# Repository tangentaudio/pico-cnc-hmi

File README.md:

# pico-cnc-hmi
Open source and open hardware HMI for LinuxCNC using USB Raw HID on a Raspberry Pi Pico 2.

# News

- rev0 PCB sent to fabrication on 2025-MAR-10.

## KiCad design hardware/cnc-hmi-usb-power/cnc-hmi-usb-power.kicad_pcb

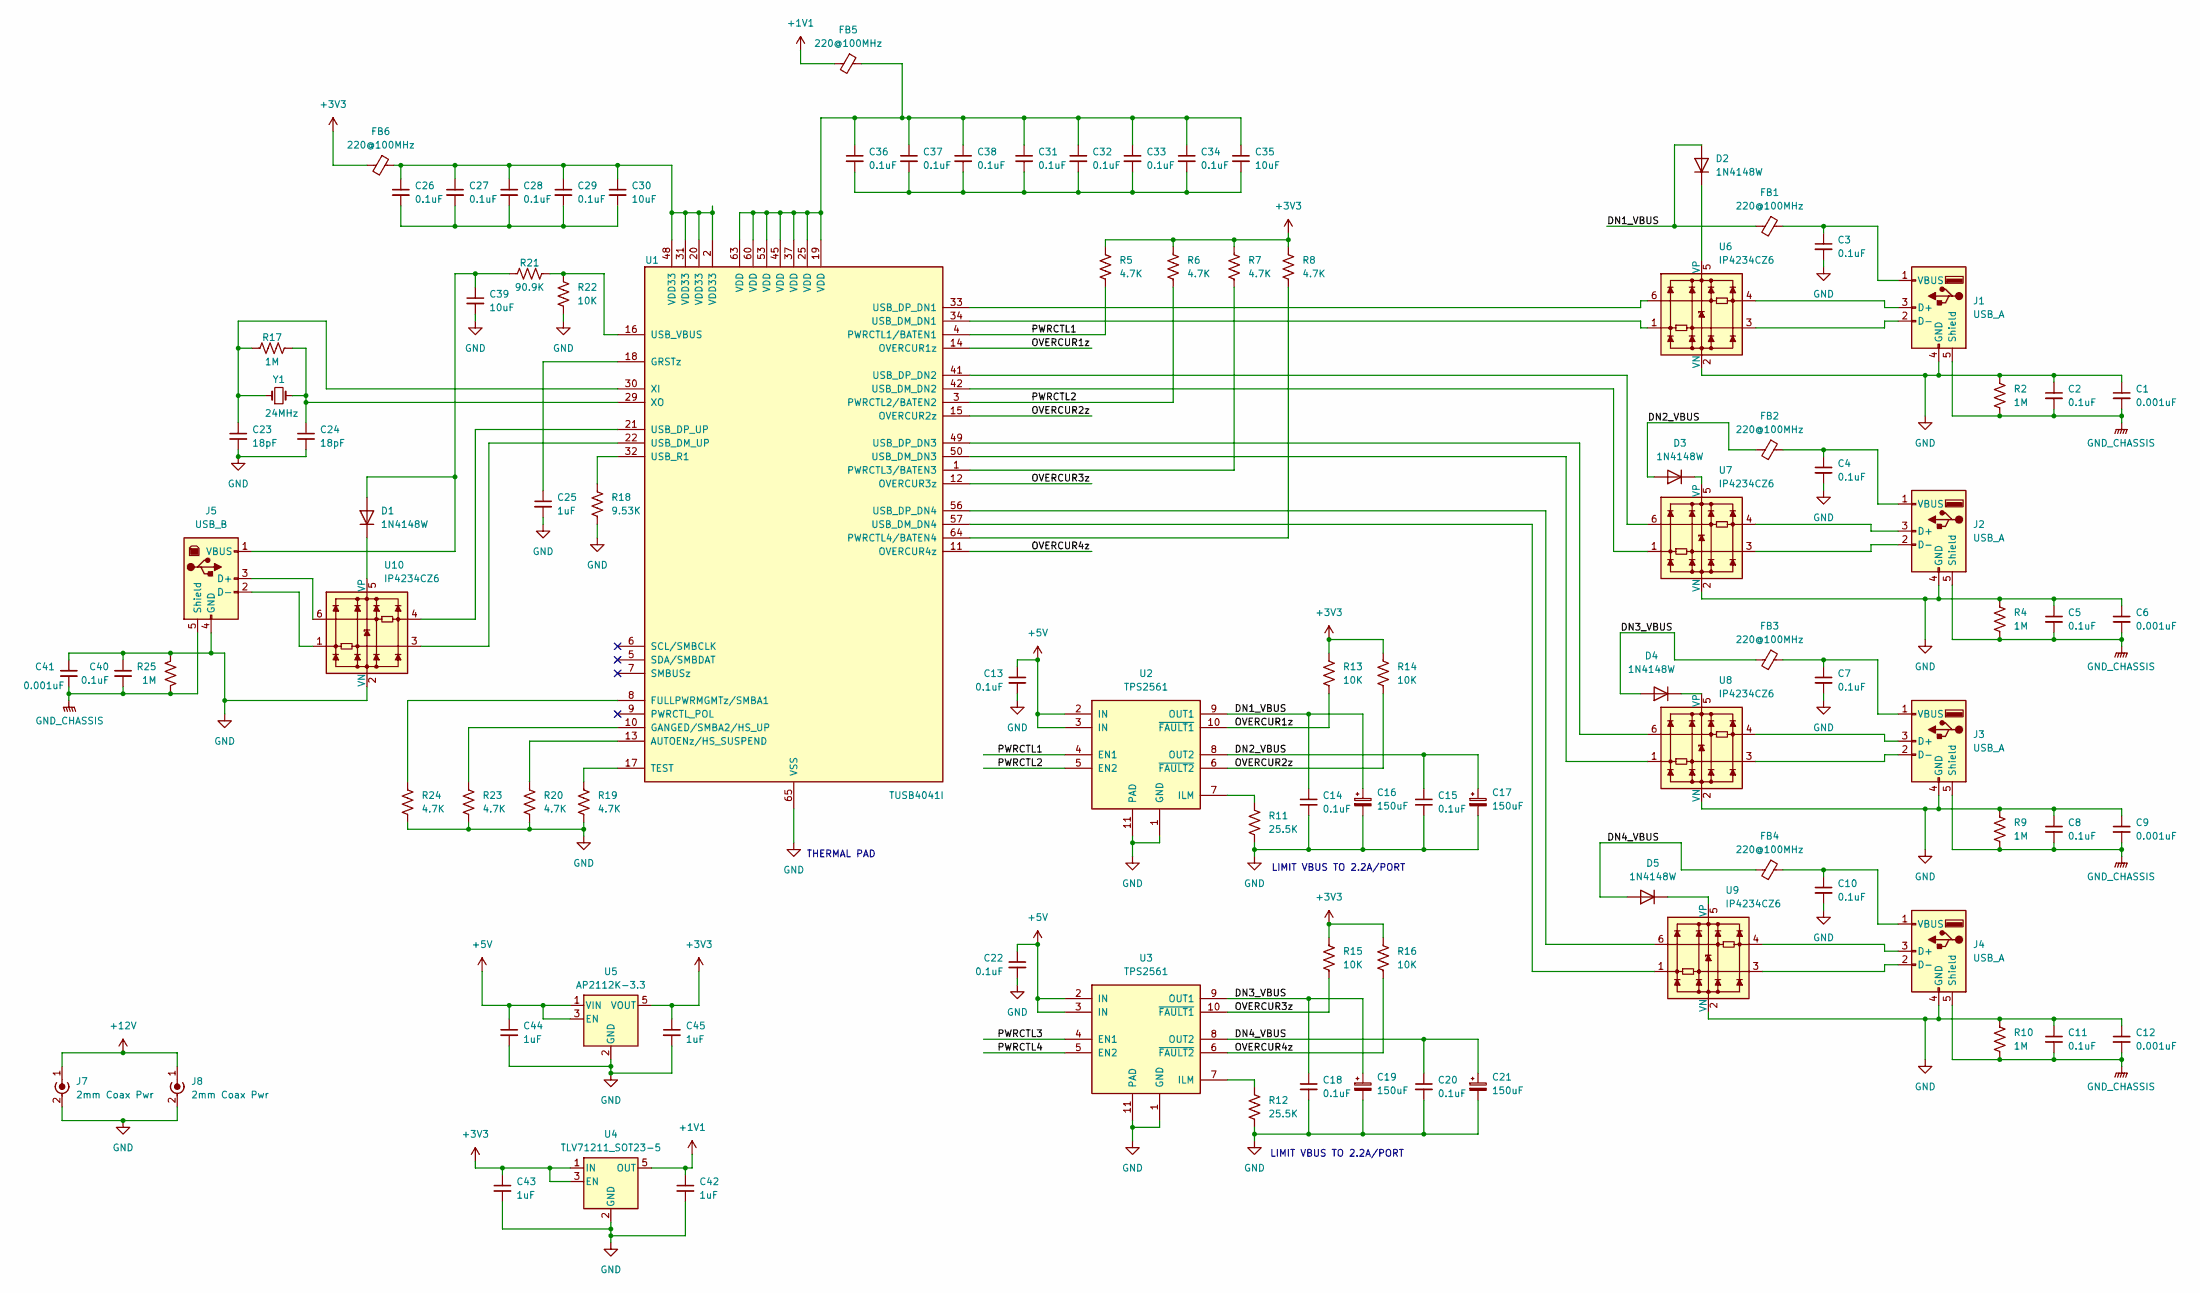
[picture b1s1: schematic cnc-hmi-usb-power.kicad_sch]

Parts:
C1, C6, C9, C12, C41: 0.001uF; C_0603_1608Metric
C2, C3, C4, C5, C7, C8, C10, C11, C13, C14, C15, C18, C20, C22, C26, C27, C28, C29, C31, C32, C33, C34, C36, C37, C38, C40: 0.1uF; C_0603_1608Metric
C16, C17, C19, C21: 150uF; CP_Elec_4x3
C23, C24: 18pF; C_0603_1608Metric
C25, C42, C43, C44, C45: 1uF; C_0805_2012Metric
C30, C35, C39: 10uF; C_0805_2012Metric
D1, D2, D3, D4, D5: 1N4148W; D_SOD-123
FB1, FB2, FB3, FB4, FB5, FB6: 220@100MHz; L_0805_2012Metric
J1, J2, J3, J4: USB_A; USB_A_Kycon_KUSBX-AS1N-B_Horizontal
J5: USB_B; USB_B_OST_USB-B1HSxx_Horizontal
J7, J8: 2mm Coax Pwr
R2, R4, R9, R10, R17, R25: 1M; R_0603_1608Metric
R5, R6, R7, R8, R19, R20, R23, R24: 4.7K; R_0603_1608Metric
R11, R12: 25.5K; R_0603_1608Metric
R13, R14, R15, R16, R22: 10K; R_0603_1608Metric
R18: 9.53K; R_0603_1608Metric
R21: 90.9K; R_0603_1608Metric
U1: TUSB4041I; HTQFP-64-1EP_10x10mm_P0.5mm_EP8x8mm_Mask4.4x4.4mm_ThermalVi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
U2, U3: TPS2561; VSON-10-1EP_3x3mm_P0.5mm_EP1.65x2.4mm_ThermalVias
U4: TLV71211_SOT23-5; SOT-23-5
U5: AP2112K-3.3; SOT-23-5
U6, U7, U8, U9, U10: IP4234CZ6; SC-74-6_1.55x2.9mm_P0.95mm
Y1: 24MHz; Crystal_SMD_0603-2Pin_6.0x3.5mm_HandSoldering

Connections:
+1V1: C42.1, FB5.2, U4.5 (OUT)
+3V3: C43.1, C45.1, FB6.2, R5.1, R6.1, R7.1, R8.1, R13.1, R14.1, R15.1, R16.1, U4.1 (IN), U4.3 (EN), U5.5 (VOUT)
+5V: C13.1, C22.1, C44.1, U2.2 (IN), U2.3 (IN), U3.2 (IN), U3.3 (IN), U5.1 (VIN), U5.3 (EN)
/DN1_VBUS: C14.1, C16.1, D2.2 (A), FB1.2, U2.9 (OUT1)
/DN2_VBUS: C15.1, C17.1, D3.2 (A), FB2.2, U2.8 (OUT2)
/DN3_VBUS: C18.1, C19.1, D4.2 (A), FB3.2, U3.9 (OUT1)
/DN4_VBUS: C20.1, C21.1, D5.2 (A), FB4.2, U3.8 (OUT2)
/OVERCUR1z: R13.2, U1.14 (OVERCUR1z), U2.10 (~FAULT1)
/OVERCUR2z: R14.2, U1.15 (OVERCUR2z), U2.6 (~FAULT2)
/OVERCUR3z: R15.2, U1.12 (OVERCUR3z), U3.10 (~FAULT1)
/OVERCUR4z: R16.2, U1.11 (OVERCUR4z), U3.6 (~FAULT2)
/PWRCTL1: R5.2, U1.4 (PWRCTL1/BATEN1), U2.4 (EN1)
/PWRCTL2: R6.2, U1.3 (PWRCTL2/BATEN2), U2.5 (EN2)
/PWRCTL3: U3.4 (EN1)
/PWRCTL4: U3.5 (EN2)
GND: C1.1, C2.1, C3.2, C4.2, C5.1, C6.1, C7.2, C8.1, C9.1, C10.2, C11.1, C12.1, C13.2, C14.2, C15.2, C16.2, C17.2, C18.2, C19.2, C20.2, C21.2, C22.2, C23.2, C24.2, C25.2, C39.2, C40.1, C41.1, C42.2, C43.2, C44.2, C45.2, J1.4 (GND), J2.4 (GND), J3.4 (GND), J4.4 (GND), J5.4 (GND), J7.2 (Ext), J8.2 (Ext), R2.1, R4.1, R9.1, R10.1, R11.2, R12.2, R18.2, R19.2, R20.2, R22.2, R23.2, R24.2, R25.1, U1.65 (VSS), U2.1 (GND), U2.11 (PAD), U3.1 (GND), U3.11 (PAD), U4.2 (GND), U5.2 (GND), U6.2 (VN), U7.2 (VN), U8.2 (VN), U9.2 (VN), U10.2 (VN)
GND_CHASSIS: C1.2, C2.2, C5.2, C6.2, C8.2, C9.2, C11.2, C12.2, C40.2, C41.2, J1.5 (Shield), J2.5 (Shield), J3.5 (Shield), J4.5 (Shield), J5.5 (Shield), R2.2, R4.2, R9.2, R10.2, R25.2
unnamed: C26.1, C27.1, C28.1, C29.1, C30.1, FB6.1, U1.2 (VDD33), U1.20 (VDD33), U1.31 (VDD33), U1.48 (VDD33)
unnamed: C26.2, C27.2, C28.2, C29.2, C30.2
unnamed: C31.1, C32.1, C33.1, C34.1, C35.1, C36.1, C37.1, C38.1, FB5.1, U1.19 (VDD), U1.25 (VDD), U1.37 (VDD), U1.45 (VDD), U1.53 (VDD), U1.60 (VDD), U1.63 (VDD)
unnamed: C31.2, C32.2, C33.2, C34.2, C35.2, C36.2, C37.2, C38.2
unnamed: C39.1, D1.2 (A), J5.1 (VBUS), R21.1
unnamed: D1.1 (K), U10.5 (VP)
unnamed: D2.1 (K), U6.5 (VP)
unnamed: D3.1 (K), U7.5 (VP)
unnamed: D4.1 (K), U8.5 (VP)
unnamed: D5.1 (K), U9.5 (VP)
unnamed: J1.3 (D+), U6.4
unnamed: J1.2 (D-), U6.3
unnamed: C3.1, FB1.1, J1.1 (VBUS)
unnamed: J2.3 (D+), U7.4
unnamed: J2.2 (D-), U7.3
unnamed: C4.1, FB2.1, J2.1 (VBUS)
unnamed: J3.3 (D+), U8.4
unnamed: J3.2 (D-), U8.3
unnamed: C7.1, FB3.1, J3.1 (VBUS)
unnamed: J4.3 (D+), U9.4
unnamed: J4.2 (D-), U9.3
unnamed: C10.1, FB4.1, J4.1 (VBUS)
unnamed: J5.3 (D+), U10.6
unnamed: J5.2 (D-), U10.1
unnamed: J7.1 (In), J8.1 (In)
unnamed: R20.1, U1.13 (AUTOENz/HS_SUSPEND)
unnamed: R24.1, U1.8 (FULLPWRMGMTz/SMBA1)
unnamed: R23.1, U1.10 (GANGED/SMBA2/HS_UP)
unnamed: C25.1, U1.18 (GRSTz)
unnamed: R7.2, U1.1 (PWRCTL3/BATEN3)
unnamed: R8.2, U1.64 (PWRCTL4/BATEN4)
unnamed: R19.1, U1.17 (TEST)
unnamed: U1.34 (USB_DM_DN1), U6.1
unnamed: U1.42 (USB_DM_DN2), U7.1
unnamed: U1.50 (USB_DM_DN3), U8.1
unnamed: U1.57 (USB_DM_DN4), U9.1
unnamed: U1.22 (USB_DM_UP), U10.3
unnamed: U1.33 (USB_DP_DN1), U6.6
unnamed: U1.41 (USB_DP_DN2), U7.6
unnamed: U1.49 (USB_DP_DN3), U8.6
unnamed: U1.56 (USB_DP_DN4), U9.6
unnamed: U1.21 (USB_DP_UP), U10.4
unnamed: R18.1, U1.32 (USB_R1)
unnamed: R21.2, R22.1, U1.16 (USB_VBUS)
unnamed: C23.1, R17.1, U1.30 (XI), Y1.1
unnamed: C24.1, R17.2, U1.29 (XO), Y1.2
unnamed: R11.1, U2.7 (ILM)
unnamed: R12.1, U3.7 (ILM)

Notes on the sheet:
LIMIT VBUS TO 2.2A/PORT
THERMAL PAD

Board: 2 copper layers, 95 parts (0 on the bottom side), 62 nets, no tracks yet.

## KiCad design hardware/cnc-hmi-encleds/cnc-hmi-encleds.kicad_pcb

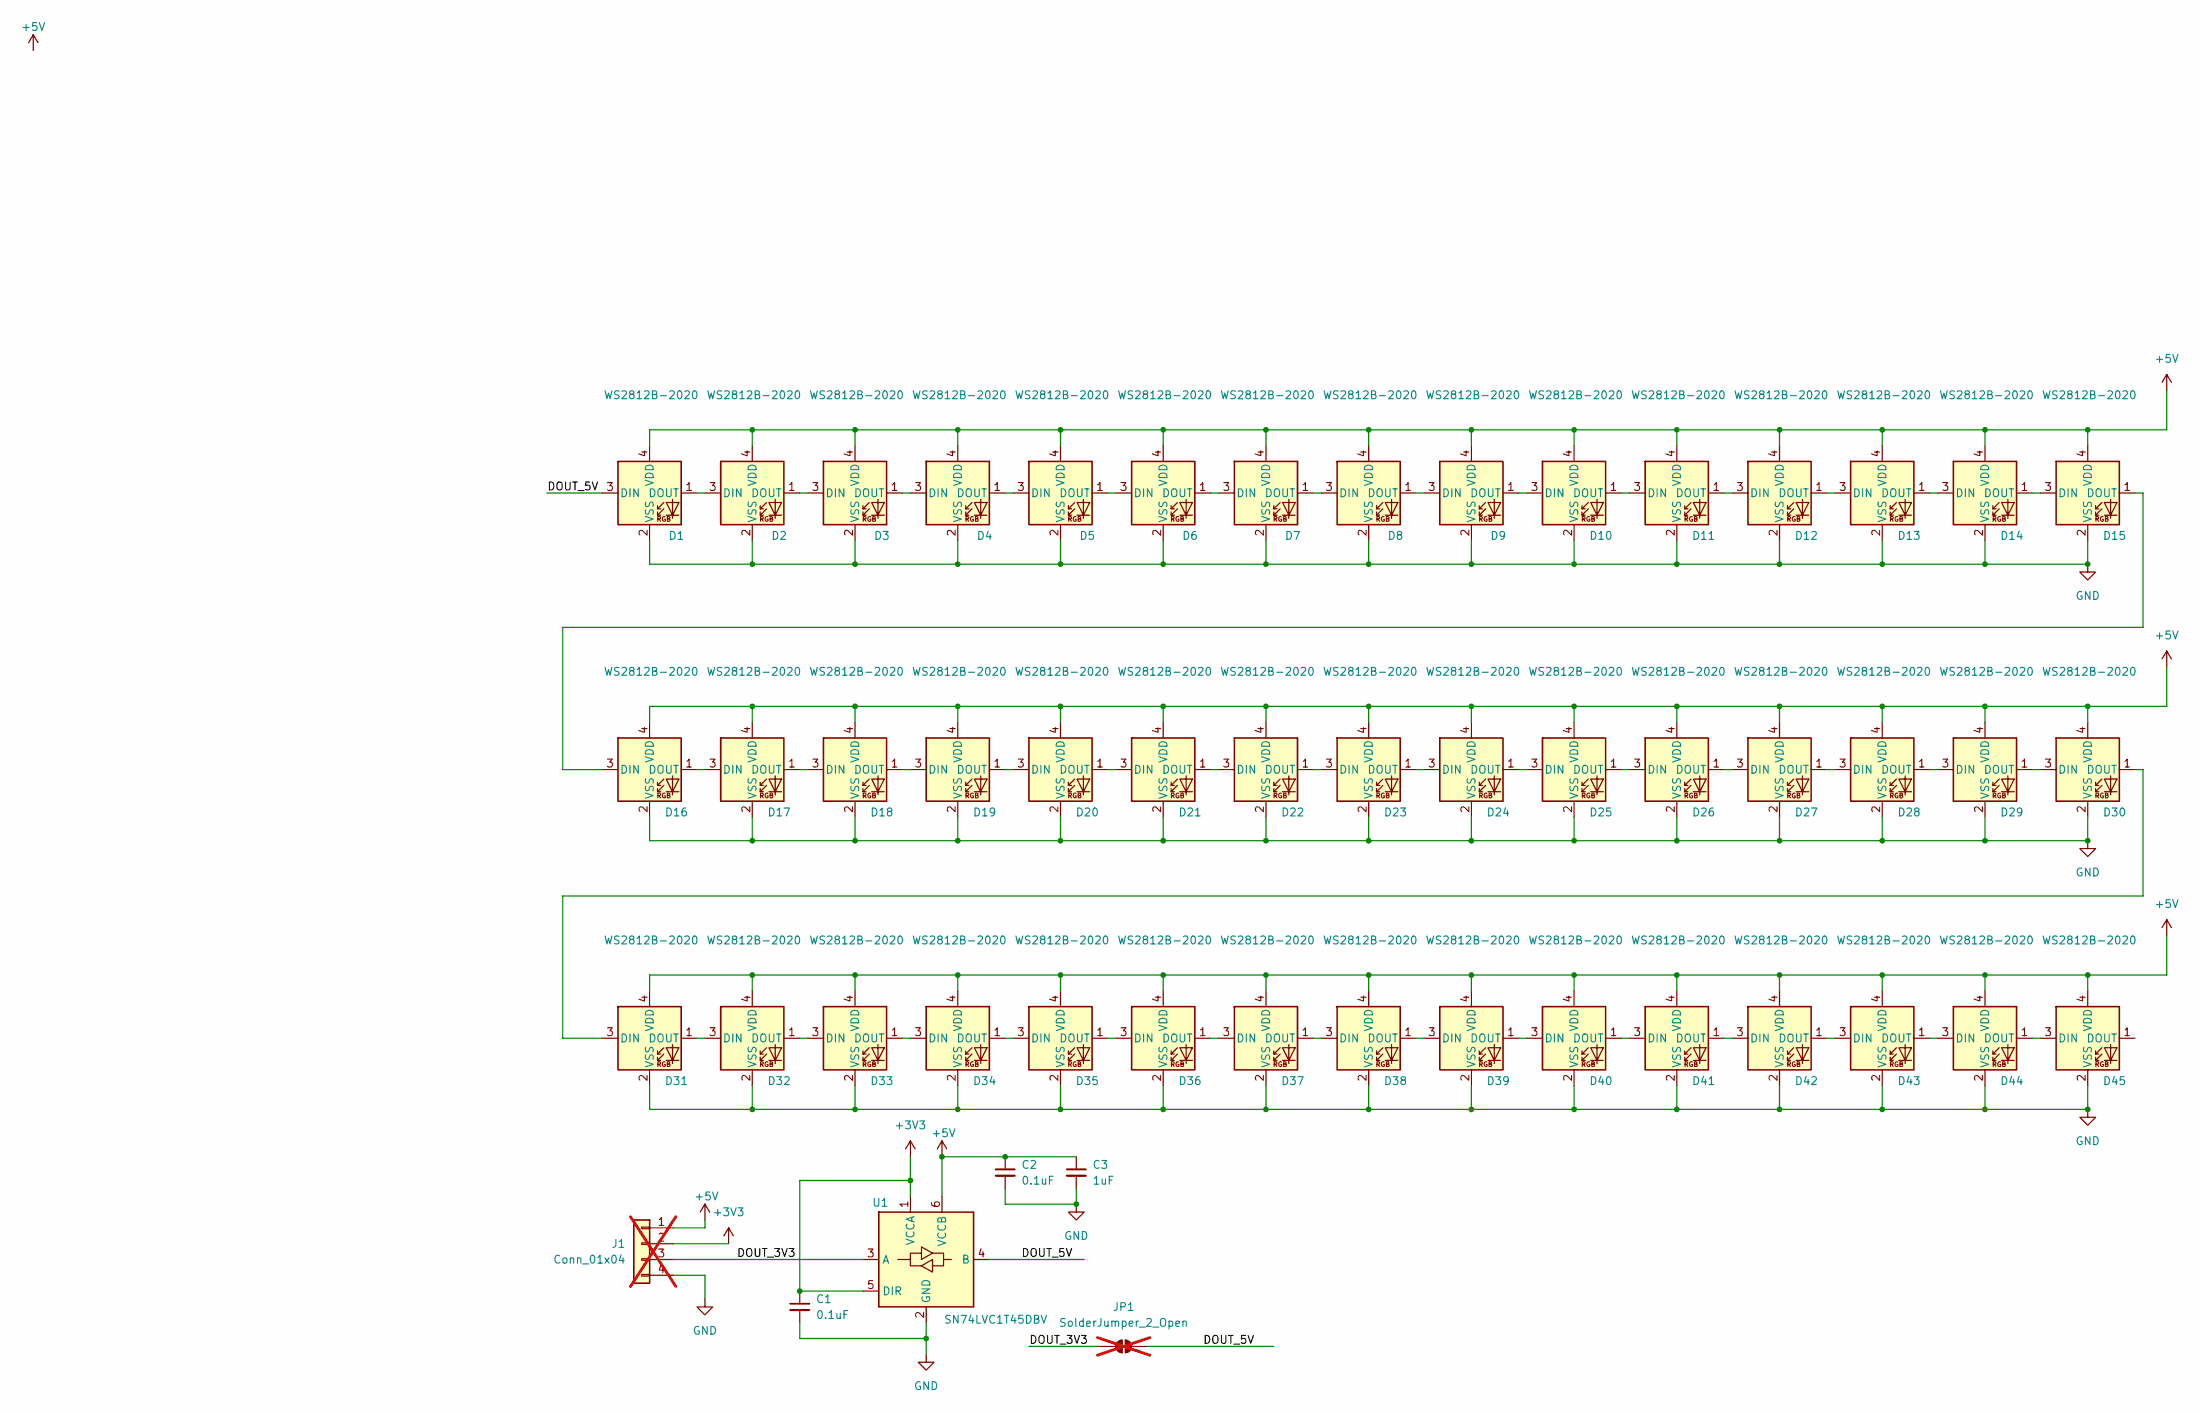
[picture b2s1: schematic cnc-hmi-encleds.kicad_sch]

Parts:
C1, C2: 0.1uF; C_0603_1608Metric; JLCPCB P/N C1590
C3: 1uF; C_0805_2012Metric; JLCPCB P/N C1712
D1, D2, D3, D4, D5, D6, D7, D8, D9, D10, D11, D12, D13, D14, D15, D16, D17, D18, D19, D20, D21, D22, D23, D24, D25, D26, D27, D28, D29, D30, D31, D32, D33, D34, D35, D36, D37, D38, D39, D40, D41, D42, D43, D44, D45: WS2812B-2020; LED_WS2812B-2020_PLCC4_2.0x2.0mm; JLCPCB P/N C965555
J1: Conn_01x04; JST_PH_B4B-PH-SM4-TB_1x04-1MP_P2.00mm_Vertical; not fitted
JP1: SolderJumper_2_Open; SolderJumper-2_P1.3mm_Open_TrianglePad1.0x1.5mm; not fitted
U1: SN74LVC1T45DBV; SOT-23-6; JLCPCB P/N C7843

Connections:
+3V3: C1.1, J1.2, U1.1 (VCCA), U1.5 (DIR)
+5V: C2.1, C3.1, D1.4 (VDD), D2.4 (VDD), D3.4 (VDD), D4.4 (VDD), D5.4 (VDD), D6.4 (VDD), D7.4 (VDD), D8.4 (VDD), D9.4 (VDD), D10.4 (VDD), D11.4 (VDD), D12.4 (VDD), D13.4 (VDD), D14.4 (VDD), D15.4 (VDD), D16.4 (VDD), D17.4 (VDD), D18.4 (VDD), D19.4 (VDD), D20.4 (VDD), D21.4 (VDD), D22.4 (VDD), D23.4 (VDD), D24.4 (VDD), D25.4 (VDD), D26.4 (VDD), D27.4 (VDD), D28.4 (VDD), D29.4 (VDD), D30.4 (VDD), D31.4 (VDD), D32.4 (VDD), D33.4 (VDD), D34.4 (VDD), D35.4 (VDD), D36.4 (VDD), D37.4 (VDD), D38.4 (VDD), D39.4 (VDD), D40.4 (VDD), D41.4 (VDD), D42.4 (VDD), D43.4 (VDD), D44.4 (VDD), D45.4 (VDD), J1.1, U1.6 (VCCB)
/DOUT_3V3: J1.3, JP1.1 (A), U1.3 (A)
/DOUT_5V: D1.3 (DIN), JP1.2 (B), U1.4 (B)
GND: C1.2, C2.2, C3.2, D1.2 (VSS), D2.2 (VSS), D3.2 (VSS), D4.2 (VSS), D5.2 (VSS), D6.2 (VSS), D7.2 (VSS), D8.2 (VSS), D9.2 (VSS), D10.2 (VSS), D11.2 (VSS), D12.2 (VSS), D13.2 (VSS), D14.2 (VSS), D15.2 (VSS), D16.2 (VSS), D17.2 (VSS), D18.2 (VSS), D19.2 (VSS), D20.2 (VSS), D21.2 (VSS), D22.2 (VSS), D23.2 (VSS), D24.2 (VSS), D25.2 (VSS), D26.2 (VSS), D27.2 (VSS), D28.2 (VSS), D29.2 (VSS), D30.2 (VSS), D31.2 (VSS), D32.2 (VSS), D33.2 (VSS), D34.2 (VSS), D35.2 (VSS), D36.2 (VSS), D37.2 (VSS), D38.2 (VSS), D39.2 (VSS), D40.2 (VSS), D41.2 (VSS), D42.2 (VSS), D43.2 (VSS), D44.2 (VSS), D45.2 (VSS), J1.4, U1.2 (GND)
unnamed: D1.1 (DOUT), D2.3 (DIN)
unnamed: D2.1 (DOUT), D3.3 (DIN)
unnamed: D3.1 (DOUT), D4.3 (DIN)
unnamed: D4.1 (DOUT), D5.3 (DIN)
unnamed: D5.1 (DOUT), D6.3 (DIN)
unnamed: D6.1 (DOUT), D7.3 (DIN)
unnamed: D7.1 (DOUT), D8.3 (DIN)
unnamed: D8.1 (DOUT), D9.3 (DIN)
unnamed: D9.1 (DOUT), D10.3 (DIN)
unnamed: D10.1 (DOUT), D11.3 (DIN)
unnamed: D11.1 (DOUT), D12.3 (DIN)
unnamed: D12.1 (DOUT), D13.3 (DIN)
unnamed: D13.1 (DOUT), D14.3 (DIN)
unnamed: D14.1 (DOUT), D15.3 (DIN)
unnamed: D15.1 (DOUT), D16.3 (DIN)
unnamed: D16.1 (DOUT), D17.3 (DIN)
unnamed: D17.1 (DOUT), D18.3 (DIN)
unnamed: D18.1 (DOUT), D19.3 (DIN)
unnamed: D19.1 (DOUT), D20.3 (DIN)
unnamed: D20.1 (DOUT), D21.3 (DIN)
unnamed: D21.1 (DOUT), D22.3 (DIN)
unnamed: D22.1 (DOUT), D23.3 (DIN)
unnamed: D23.1 (DOUT), D24.3 (DIN)
unnamed: D24.1 (DOUT), D25.3 (DIN)
unnamed: D25.1 (DOUT), D26.3 (DIN)
unnamed: D26.1 (DOUT), D27.3 (DIN)
unnamed: D27.1 (DOUT), D28.3 (DIN)
unnamed: D28.1 (DOUT), D29.3 (DIN)
unnamed: D29.1 (DOUT), D30.3 (DIN)
unnamed: D30.1 (DOUT), D31.3 (DIN)
unnamed: D31.1 (DOUT), D32.3 (DIN)
unnamed: D32.1 (DOUT), D33.3 (DIN)
unnamed: D33.1 (DOUT), D34.3 (DIN)
unnamed: D34.1 (DOUT), D35.3 (DIN)
unnamed: D35.1 (DOUT), D36.3 (DIN)
unnamed: D36.1 (DOUT), D37.3 (DIN)
unnamed: D37.1 (DOUT), D38.3 (DIN)
unnamed: D38.1 (DOUT), D39.3 (DIN)
unnamed: D39.1 (DOUT), D40.3 (DIN)
unnamed: D40.1 (DOUT), D41.3 (DIN)
unnamed: D41.1 (DOUT), D42.3 (DIN)
unnamed: D42.1 (DOUT), D43.3 (DIN)
unnamed: D43.1 (DOUT), D44.3 (DIN)
unnamed: D44.1 (DOUT), D45.3 (DIN)

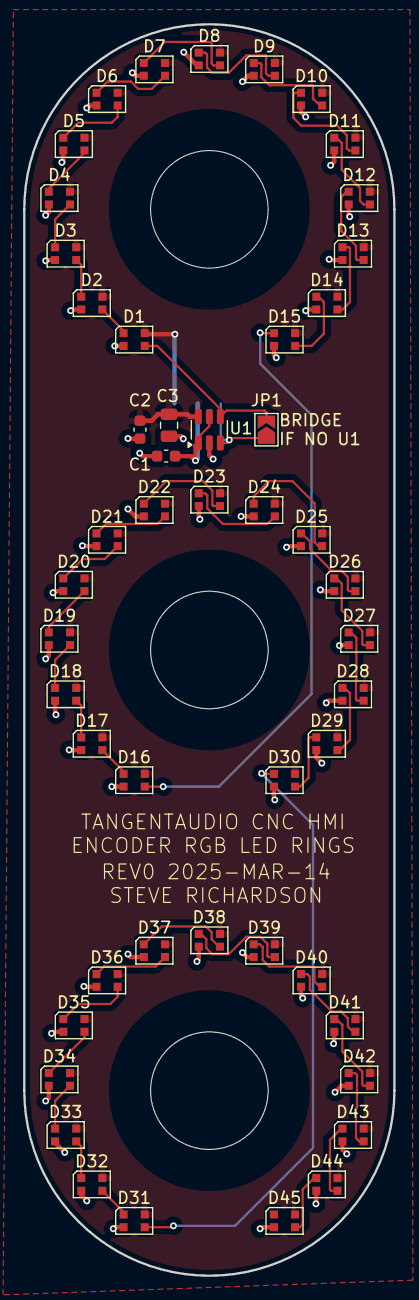
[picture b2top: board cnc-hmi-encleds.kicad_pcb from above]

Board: 2 copper layers, 32.0 x 108.2 mm, 51 parts (1 on the bottom side), 49 nets.

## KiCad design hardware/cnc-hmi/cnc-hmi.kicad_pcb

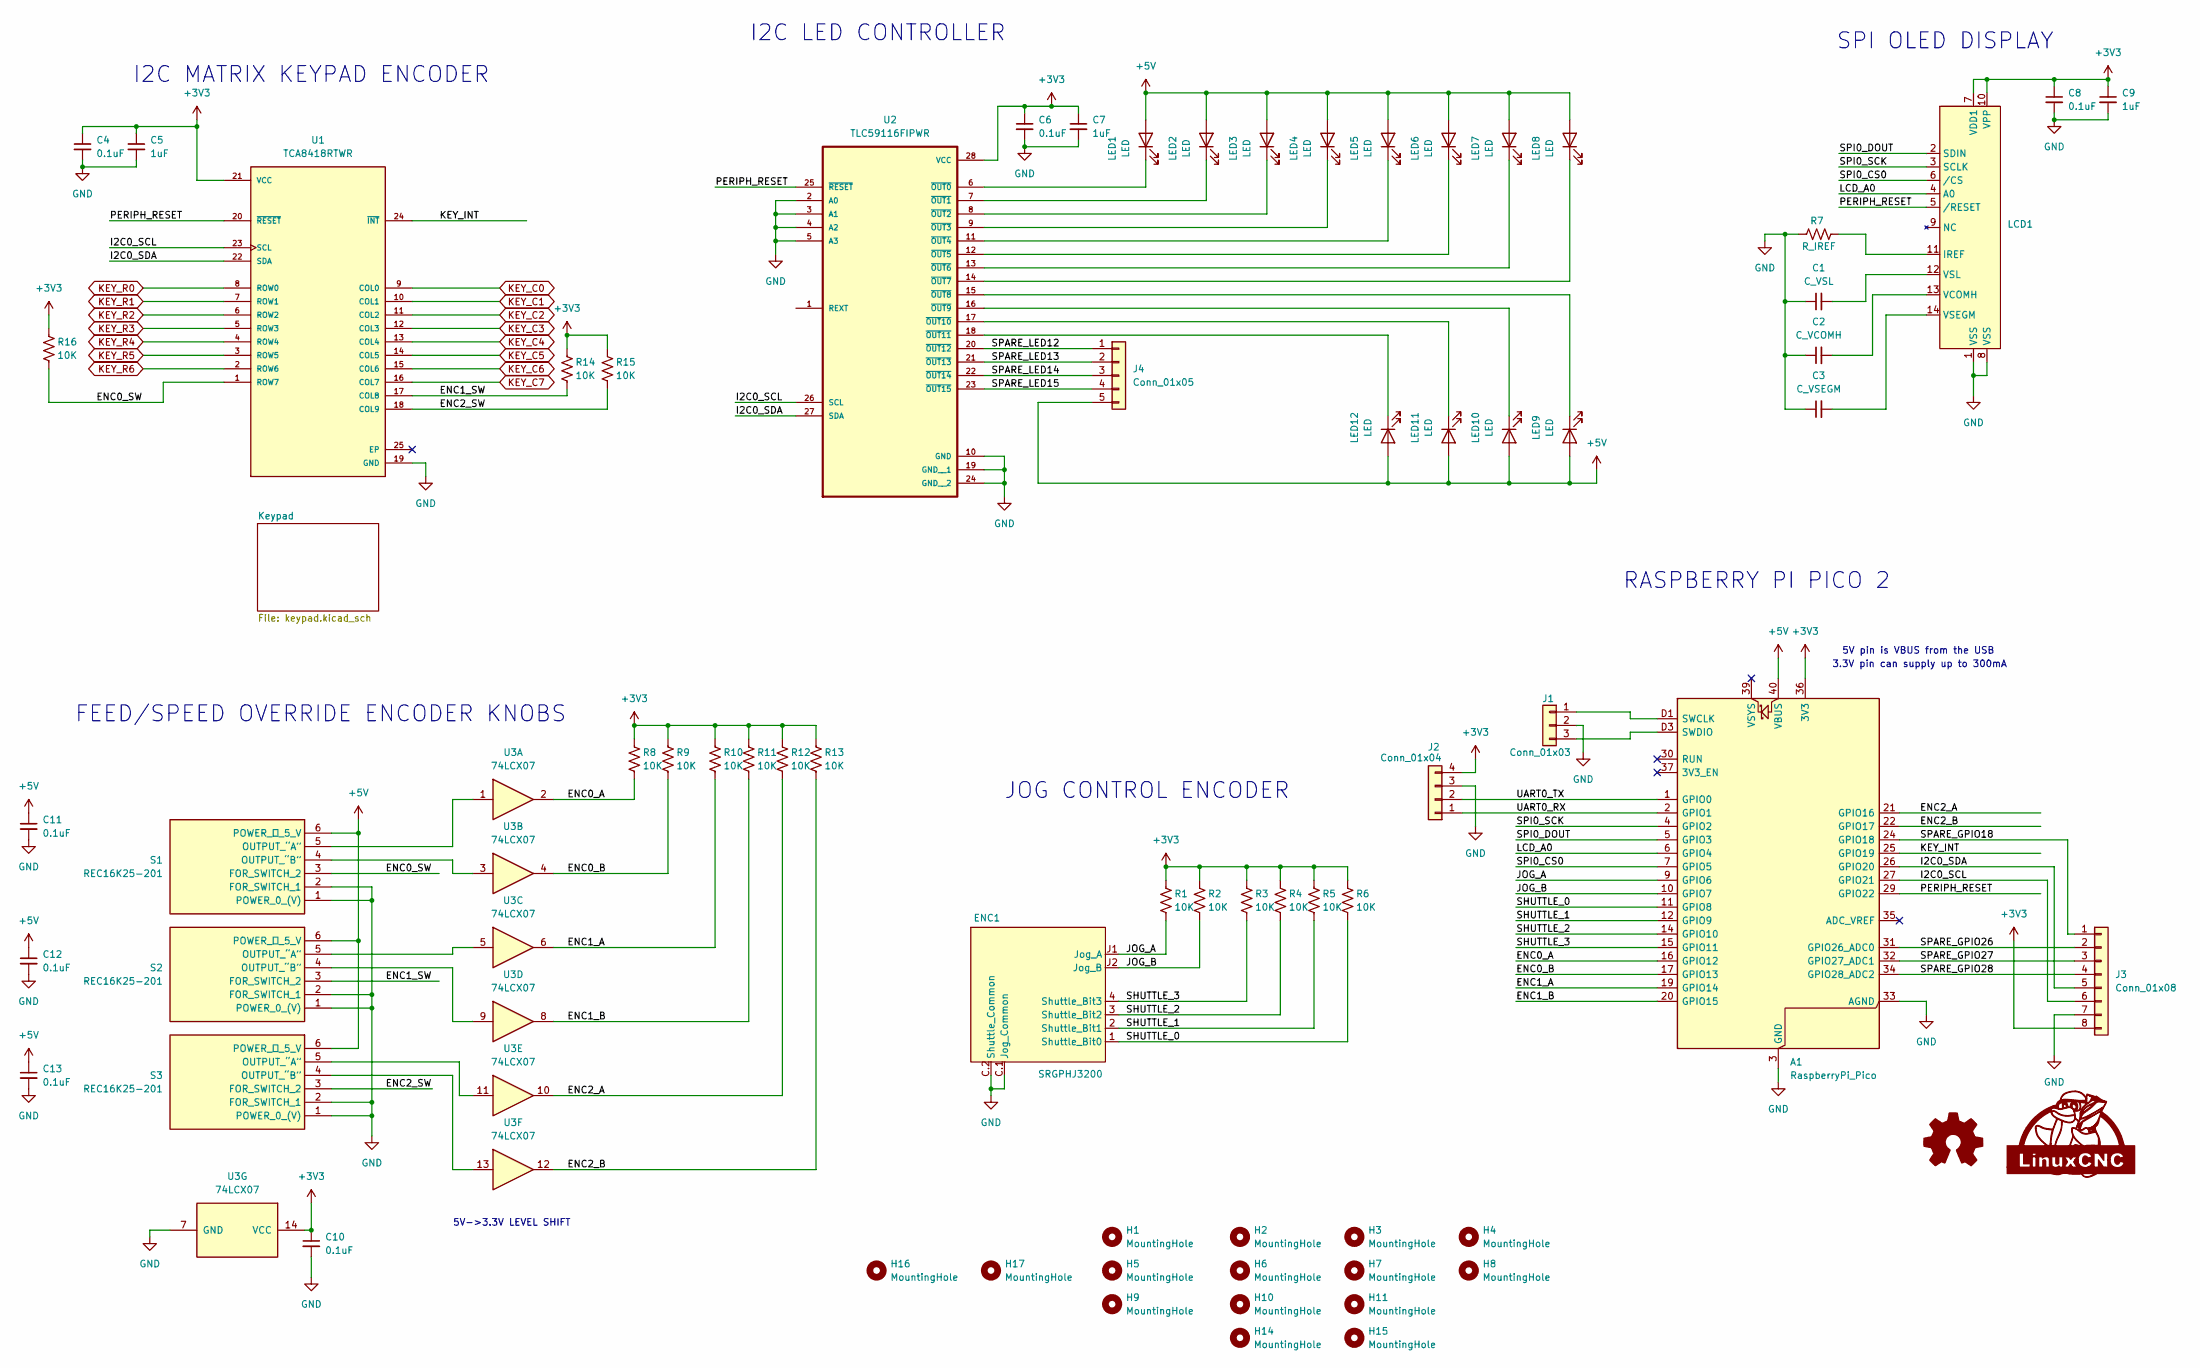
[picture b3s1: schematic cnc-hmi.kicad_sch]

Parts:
A1: RaspberryPi_Pico; RaspberryPi_Pico2_SMD_HandSolder
C1: C_VSL; C_0805_2012Metric_Pad1.18x1.45mm_HandSolder
C2: C_VCOMH; C_0805_2012Metric_Pad1.18x1.45mm_HandSolder
C3: C_VSEGM; C_0805_2012Metric_Pad1.18x1.45mm_HandSolder
C4, C6, C8, C10, C11, C12, C13: 0.1uF; C_0603_1608Metric
C5, C7, C9: 1uF; C_0805_2012Metric
ENC1: SRGPHJ3200
H1, H2, H3, H4, H5, H6, H7, H8, H9, H10, H11, H14, H15: MountingHole; M3-Mounting Hole
H16, H17: MountingHole; M2.5-Mounting Hole
J1: Conn_01x03; JST_PH_S3B-PH-K_1x03_P2.00mm_Horizontal
J2: Conn_01x04; JST_PH_S4B-PH-K_1x04_P2.00mm_Horizontal
J3: Conn_01x08; JST_PH_S8B-PH-K_1x08_P2.00mm_Horizontal
J4: Conn_01x05; JST_PH_S5B-PH-K_1x05_P2.00mm_Horizontal
LCD1: ER-CON14HT-1
LED1, LED2, LED3, LED4, LED5, LED6, LED7, LED8, LED9, LED10, LED11, LED12: LED; MX-LED-Reversed
LOGO1: LinuxCNC Logo
LOGO2: Logo_Open_Hardware_Small; OSHW-Logo_11.4x12mm_SilkScreen
R1, R2, R3, R4, R5, R6, R8, R9, R10, R11, R12, R13, R14, R15, R16: 10K; R_0603_1608Metric
R7: R_IREF; R_0603_1608Metric
S1, S2, S3: REC16K25-201; REC16K25201; Manufacturer_Part_Number REC16K25-201
U1: TCA8418RTWR; QFN50P400X400X80-25N; PARTREV G
U2: TLC59116FIPWR; SOP65P640X120-28N
U3: 74LCX07; SOIC-14_3.9x8.7mm_P1.27mm

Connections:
+3V3: A1.36 (3V3), C4.1, C5.1, C6.1, C7.1, C8.1, C9.1, C10.1, J2.4, J3.8, LCD1.7 (VDD1), LCD1.10 (VPP), R1.1, R2.1, R3.1, R4.1, R5.1, R6.1, R8.1, R9.1, R10.1, R11.1, R12.1, R13.1, R14.1, R15.1, R16.1, U1.21 (VCC), U2.28 (VCC), U3.14 (VCC)
+5V: A1.40 (VBUS), C11.1, C12.1, C13.1, J4.5, LED1.2 (A), LED2.2 (A), LED3.2 (A), LED4.2 (A), LED5.2 (A), LED6.2 (A), LED7.2 (A), LED8.2 (A), LED9.2 (A), LED10.2 (A), LED11.2 (A), LED12.2 (A), S1.6 (POWER_＋_5_V), S2.6 (POWER_＋_5_V), S3.6 (POWER_＋_5_V)
/ENC0_A: A1.16 (GPIO12), R8.2, U3.2
/ENC0_B: A1.17 (GPIO13), R9.2, U3.4
/ENC0_SW: R16.2, S1.3 (FOR_SWITCH_2), U1.1 (ROW7)
/ENC1_A: A1.19 (GPIO14), R10.2, U3.6
/ENC1_B: A1.20 (GPIO15), R11.2, U3.8
/ENC1_SW: R14.2, S2.3 (FOR_SWITCH_2), U1.17 (COL8)
/ENC2_A: A1.21 (GPIO16), R12.2, U3.10
/ENC2_B: A1.22 (GPIO17), R13.2, U3.12
/ENC2_SW: R15.2, S3.3 (FOR_SWITCH_2), U1.18 (COL9)
/I2C0_SCL: A1.27 (GPIO21), J3.6, U1.23 (SCL), U2.26 (SCL)
/I2C0_SDA: A1.26 (GPIO20), J3.5, U1.22 (SDA), U2.27 (SDA)
/JOG_A: A1.9 (GPIO6), ENC1.J1 (Jog_A), R1.2
/JOG_B: A1.10 (GPIO7), ENC1.J2 (Jog_B), R2.2
/KEY_INT: A1.25 (GPIO19), U1.24 (~INT)
/LCD_A0: A1.6 (GPIO4), LCD1.4 (A0)
/PERIPH_RESET: A1.29 (GPIO22), LCD1.5 (/RESET), U1.20 (~RESET), U2.25 (~RESET)
/SHUTTLE_0: A1.11 (GPIO8), ENC1.1 (Shuttle_Bit0), R6.2
/SHUTTLE_1: A1.12 (GPIO9), ENC1.2 (Shuttle_Bit1), R5.2
/SHUTTLE_2: A1.14 (GPIO10), ENC1.3 (Shuttle_Bit2), R4.2
/SHUTTLE_3: A1.15 (GPIO11), ENC1.4 (Shuttle_Bit3), R3.2
/SPARE_GPIO18: A1.24 (GPIO18), J3.1
/SPARE_GPIO26: A1.31 (GPIO26_ADC0), J3.2
/SPARE_GPIO27: A1.32 (GPIO27_ADC1), J3.3
/SPARE_GPIO28: A1.34 (GPIO28_ADC2), J3.4
/SPARE_LED12: J4.1, U2.20 (~OUT12)
/SPARE_LED13: J4.2, U2.21 (~OUT13)
/SPARE_LED14: J4.3, U2.22 (~OUT14)
/SPARE_LED15: J4.4, U2.23 (~OUT15)
/SPI0_CS0: A1.7 (GPIO5), LCD1.6 (/CS)
/SPI0_DOUT: A1.5 (GPIO3), LCD1.2 (SDIN)
/SPI0_SCK: A1.4 (GPIO2), LCD1.3 (SCLK)
/UART0_RX: A1.2 (GPIO1), J2.1
/UART0_TX: A1.1 (GPIO0), J2.2
GND: A1.3 (GND), A1.8 (GND), A1.13 (GND), A1.18 (GND), A1.23 (GND), A1.28 (GND), A1.33 (AGND), A1.38 (GND), A1.D2 (GND), C1.1, C2.1, C3.1, C4.2, C5.2, C6.2, C7.2, C8.2, C9.2, C10.2, C11.2, C12.2, C13.2, ENC1.C.1 (Jog_Common), ENC1.C.2 (Shuttle_Common), J1.2, J2.3, J3.7, LCD1.1 (VSS), LCD1.8 (VSS), R7.1, S1.1 (POWER_0_(V)), S1.2 (FOR_SWITCH_1), S2.1 (POWER_0_(V)), S2.2 (FOR_SWITCH_1), S3.1 (POWER_0_(V)), S3.2 (FOR_SWITCH_1), U1.19 (GND), U2.2 (A0), U2.3 (A1), U2.4 (A2), U2.5 (A3), U2.10 (GND), U2.19 (GND__1), U2.24 (GND__2), U3.7 (GND)
KEY_C0: U1.9 (COL0); also elsewhere on the board
KEY_C1: U1.10 (COL1); also elsewhere on the board
KEY_C2: U1.11 (COL2); also elsewhere on the board
KEY_C3: U1.12 (COL3); also elsewhere on the board
KEY_C4: U1.13 (COL4); also elsewhere on the board
KEY_C5: U1.14 (COL5); also elsewhere on the board
KEY_C6: U1.15 (COL6); also elsewhere on the board
KEY_C7: U1.16 (COL7); also elsewhere on the board
KEY_R0: U1.8 (ROW0); also elsewhere on the board
KEY_R1: U1.7 (ROW1); also elsewhere on the board
KEY_R2: U1.6 (ROW2); also elsewhere on the board
KEY_R3: U1.5 (ROW3); also elsewhere on the board
KEY_R4: U1.4 (ROW4); also elsewhere on the board
KEY_R5: U1.3 (ROW5); also elsewhere on the board
KEY_R6: U1.2 (ROW6); also elsewhere on the board
unnamed: A1.D1 (SWCLK), J1.1
unnamed: A1.D3 (SWDIO), J1.3
unnamed: LCD1.11 (IREF), R7.2
unnamed: C2.2, LCD1.13 (VCOMH)
unnamed: C3.2, LCD1.14 (VSEGM)
unnamed: C1.2, LCD1.12 (VSL)
unnamed: LED1.1 (K), U2.6 (~OUT0)
unnamed: LED2.1 (K), U2.7 (~OUT1)
unnamed: LED3.1 (K), U2.8 (~OUT2)
unnamed: LED4.1 (K), U2.9 (~OUT3)
unnamed: LED5.1 (K), U2.11 (~OUT4)
unnamed: LED6.1 (K), U2.12 (~OUT5)
unnamed: LED7.1 (K), U2.13 (~OUT6)
unnamed: LED8.1 (K), U2.14 (~OUT7)
unnamed: LED9.1 (K), U2.15 (~OUT8)
unnamed: LED10.1 (K), U2.16 (~OUT9)
unnamed: LED11.1 (K), U2.17 (~OUT10)
unnamed: LED12.1 (K), U2.18 (~OUT11)
unnamed: S1.5 (OUTPUT_“A”), U3.1
unnamed: S1.4 (OUTPUT_“B”), U3.3
unnamed: S2.5 (OUTPUT_“A”), U3.5
unnamed: S2.4 (OUTPUT_“B”), U3.9
unnamed: S3.5 (OUTPUT_“A”), U3.11
unnamed: S3.4 (OUTPUT_“B”), U3.13

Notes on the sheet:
3.3V pin can supply up to 300mA
SPI OLED DISPLAY
FEED/SPEED OVERRIDE ENCODER KNOBS
RASPBERRY PI PICO 2
5V->3.3V LEVEL SHIFT
JOG CONTROL ENCODER
5V pin is VBUS from the USB
I2C LED CONTROLLER
I2C MATRIX KEYPAD ENCODER

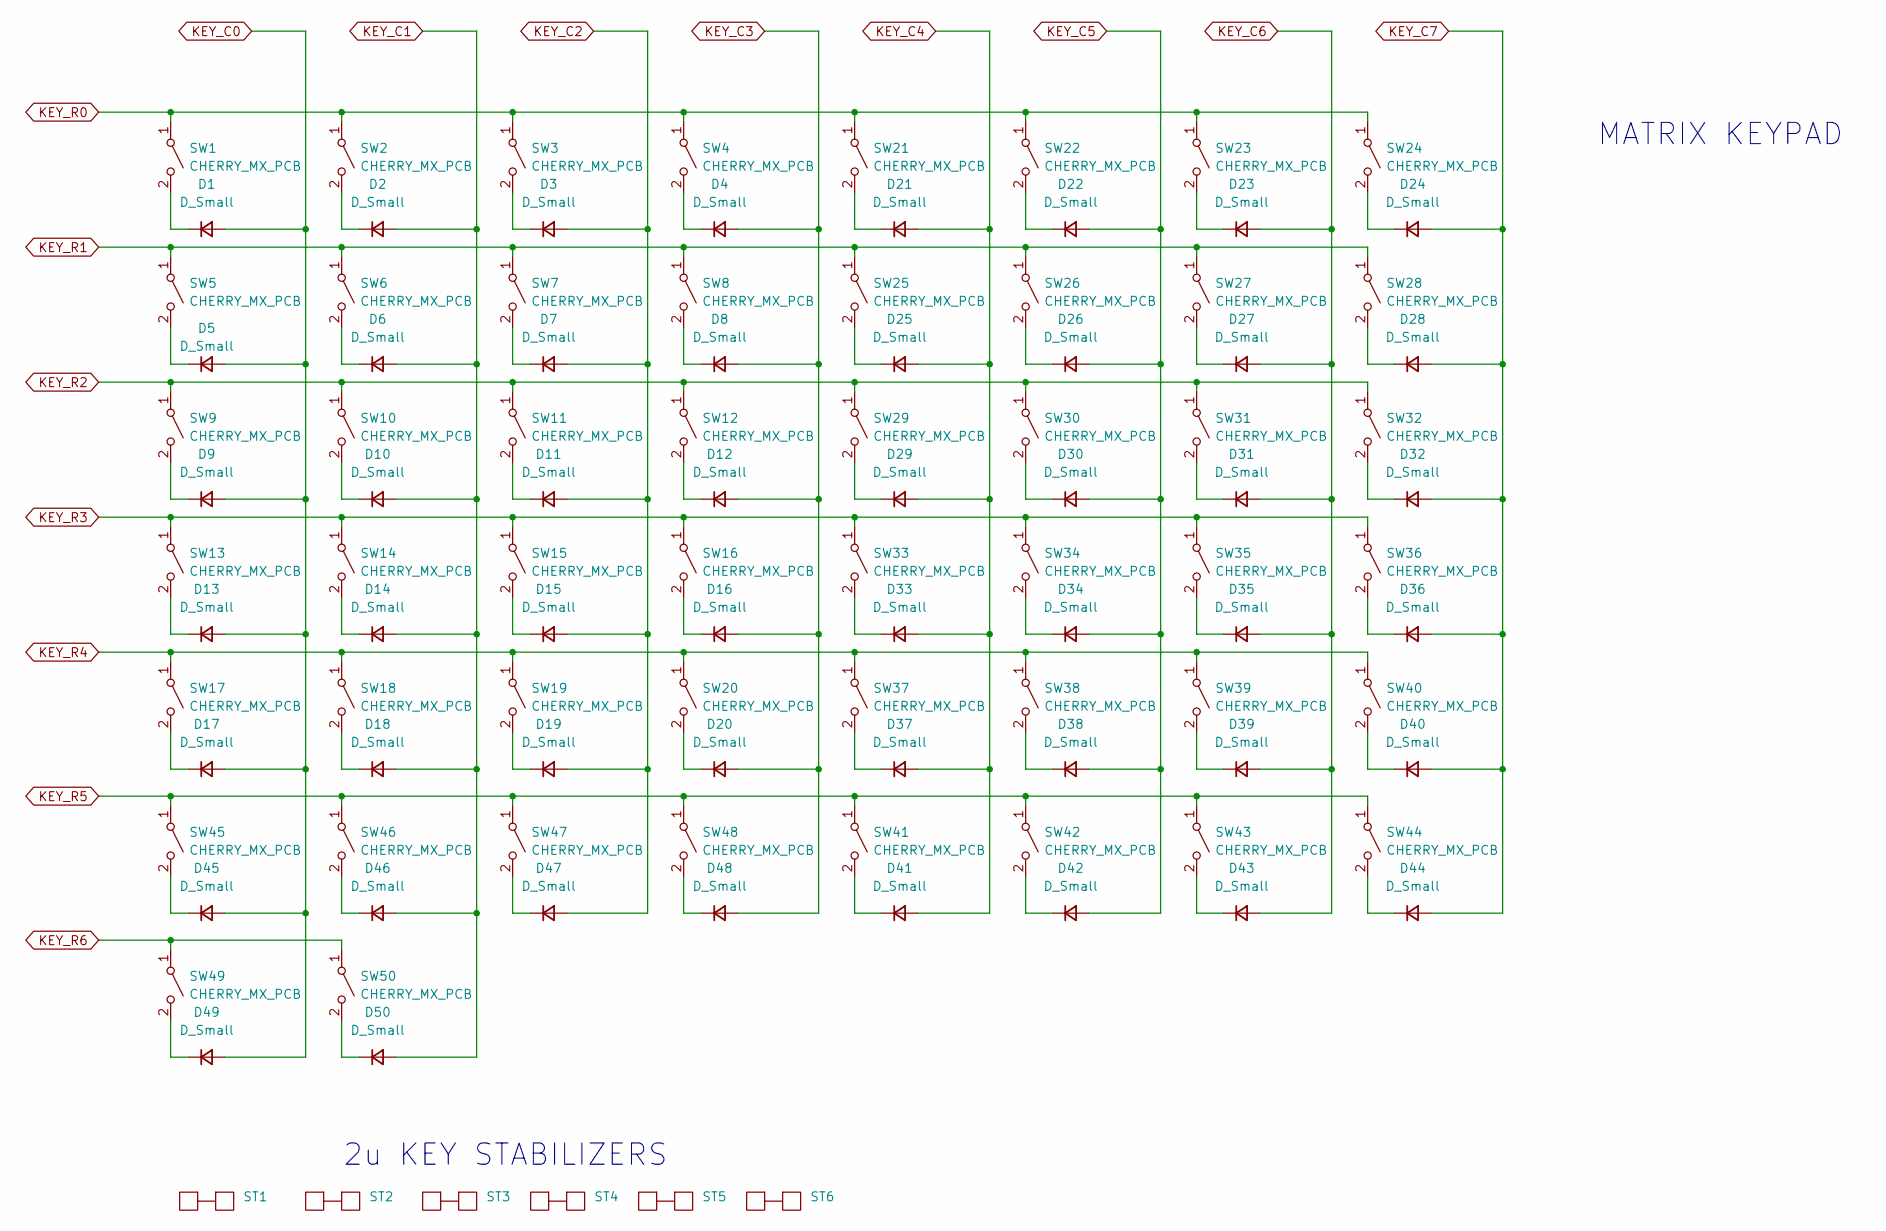
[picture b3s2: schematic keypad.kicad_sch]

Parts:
D1, D2, D3, D4, D5, D6, D7, D8, D9, D10, D11, D12, D13, D14, D15, D16, D17, D18, D19, D20, D21, D22, D23, D24, D25, D26, D27, D28, D29, D30, D31, D32, D33, D34, D35, D36, D37, D38, D39, D40, D41, D42, D43, D44, D45, D46, D47, D48, D49, D50: D_Small; D_SOD-523
ST1, ST2, ST3, ST4, ST5, ST6: Stabilizer_Cherry_MX_2.00u
SW1, SW2, SW3, SW4, SW5, SW6, SW7, SW8, SW9, SW10, SW11, SW12, SW13, SW14, SW15, SW17, SW18, SW19, SW20, SW21, SW22, SW23, SW24, SW25, SW26, SW27, SW28, SW29, SW30, SW31, SW32, SW33, SW34, SW35, SW36, SW37, SW39, SW40, SW41, SW42, SW43, SW44, SW49, SW50: CHERRY_MX_PCB; SW_Cherry_MX_PCB_1.00u
SW16: CHERRY_MX_PCB; SW_Cherry_MX_PCB_2.00u_90deg
SW38, SW45, SW46, SW47, SW48: CHERRY_MX_PCB; SW_Cherry_MX_PCB_2.00u

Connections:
KEY_C0: D1.2 (A), D5.2 (A), D9.2 (A), D13.2 (A), D17.2 (A), D45.2 (A), D49.2 (A); also elsewhere on the board
KEY_C1: D2.2 (A), D6.2 (A), D10.2 (A), D14.2 (A), D18.2 (A), D46.2 (A), D50.2 (A); also elsewhere on the board
KEY_C2: D3.2 (A), D7.2 (A), D11.2 (A), D15.2 (A), D19.2 (A), D47.2 (A); also elsewhere on the board
KEY_C3: D4.2 (A), D8.2 (A), D12.2 (A), D16.2 (A), D20.2 (A), D48.2 (A); also elsewhere on the board
KEY_C4: D21.2 (A), D25.2 (A), D29.2 (A), D33.2 (A), D37.2 (A), D41.2 (A); also elsewhere on the board
KEY_C5: D22.2 (A), D26.2 (A), D30.2 (A), D34.2 (A), D38.2 (A), D42.2 (A); also elsewhere on the board
KEY_C6: D23.2 (A), D27.2 (A), D31.2 (A), D35.2 (A), D39.2 (A), D43.2 (A); also elsewhere on the board
KEY_C7: D24.2 (A), D28.2 (A), D32.2 (A), D36.2 (A), D40.2 (A), D44.2 (A); also elsewhere on the board
KEY_R0: SW1.1 (A), SW2.1 (A), SW3.1 (A), SW4.1 (A), SW21.1 (A), SW22.1 (A), SW23.1 (A), SW24.1 (A); also elsewhere on the board
KEY_R1: SW5.1 (A), SW6.1 (A), SW7.1 (A), SW8.1 (A), SW25.1 (A), SW26.1 (A), SW27.1 (A), SW28.1 (A); also elsewhere on the board
KEY_R2: SW9.1 (A), SW10.1 (A), SW11.1 (A), SW12.1 (A), SW29.1 (A), SW30.1 (A), SW31.1 (A), SW32.1 (A); also elsewhere on the board
KEY_R3: SW13.1 (A), SW14.1 (A), SW15.1 (A), SW16.1 (A), SW33.1 (A), SW34.1 (A), SW35.1 (A), SW36.1 (A); also elsewhere on the board
KEY_R4: SW17.1 (A), SW18.1 (A), SW19.1 (A), SW20.1 (A), SW37.1 (A), SW38.1 (A), SW39.1 (A), SW40.1 (A); also elsewhere on the board
KEY_R5: SW41.1 (A), SW42.1 (A), SW43.1 (A), SW44.1 (A), SW45.1 (A), SW46.1 (A), SW47.1 (A), SW48.1 (A); also elsewhere on the board
KEY_R6: SW49.1 (A), SW50.1 (A); also elsewhere on the board
unnamed: D1.1 (K), SW1.2 (B)
unnamed: D2.1 (K), SW2.2 (B)
unnamed: D3.1 (K), SW3.2 (B)
unnamed: D4.1 (K), SW4.2 (B)
unnamed: D5.1 (K), SW5.2 (B)
unnamed: D6.1 (K), SW6.2 (B)
unnamed: D7.1 (K), SW7.2 (B)
unnamed: D8.1 (K), SW8.2 (B)
unnamed: D9.1 (K), SW9.2 (B)
unnamed: D10.1 (K), SW10.2 (B)
unnamed: D11.1 (K), SW11.2 (B)
unnamed: D12.1 (K), SW12.2 (B)
unnamed: D13.1 (K), SW13.2 (B)
unnamed: D14.1 (K), SW14.2 (B)
unnamed: D15.1 (K), SW15.2 (B)
unnamed: D16.1 (K), SW16.2 (B)
unnamed: D17.1 (K), SW17.2 (B)
unnamed: D18.1 (K), SW18.2 (B)
unnamed: D19.1 (K), SW19.2 (B)
unnamed: D20.1 (K), SW20.2 (B)
unnamed: D21.1 (K), SW21.2 (B)
unnamed: D22.1 (K), SW22.2 (B)
unnamed: D23.1 (K), SW23.2 (B)
unnamed: D24.1 (K), SW24.2 (B)
unnamed: D25.1 (K), SW25.2 (B)
unnamed: D26.1 (K), SW26.2 (B)
unnamed: D27.1 (K), SW27.2 (B)
unnamed: D28.1 (K), SW28.2 (B)
unnamed: D29.1 (K), SW29.2 (B)
unnamed: D30.1 (K), SW30.2 (B)
unnamed: D31.1 (K), SW31.2 (B)
unnamed: D32.1 (K), SW32.2 (B)
unnamed: D33.1 (K), SW33.2 (B)
unnamed: D34.1 (K), SW34.2 (B)
unnamed: D35.1 (K), SW35.2 (B)
unnamed: D36.1 (K), SW36.2 (B)
unnamed: D37.1 (K), SW37.2 (B)
unnamed: D38.1 (K), SW38.2 (B)
unnamed: D39.1 (K), SW39.2 (B)
unnamed: D40.1 (K), SW40.2 (B)
unnamed: D41.1 (K), SW41.2 (B)
unnamed: D42.1 (K), SW42.2 (B)
unnamed: D43.1 (K), SW43.2 (B)
unnamed: D44.1 (K), SW44.2 (B)
unnamed: D45.1 (K), SW45.2 (B)
unnamed: D46.1 (K), SW46.2 (B)
unnamed: D47.1 (K), SW47.2 (B)
unnamed: D48.1 (K), SW48.2 (B)
unnamed: D49.1 (K), SW49.2 (B)
unnamed: D50.1 (K), SW50.2 (B)

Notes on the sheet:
MATRIX KEYPAD
2u KEY STABILIZERS
